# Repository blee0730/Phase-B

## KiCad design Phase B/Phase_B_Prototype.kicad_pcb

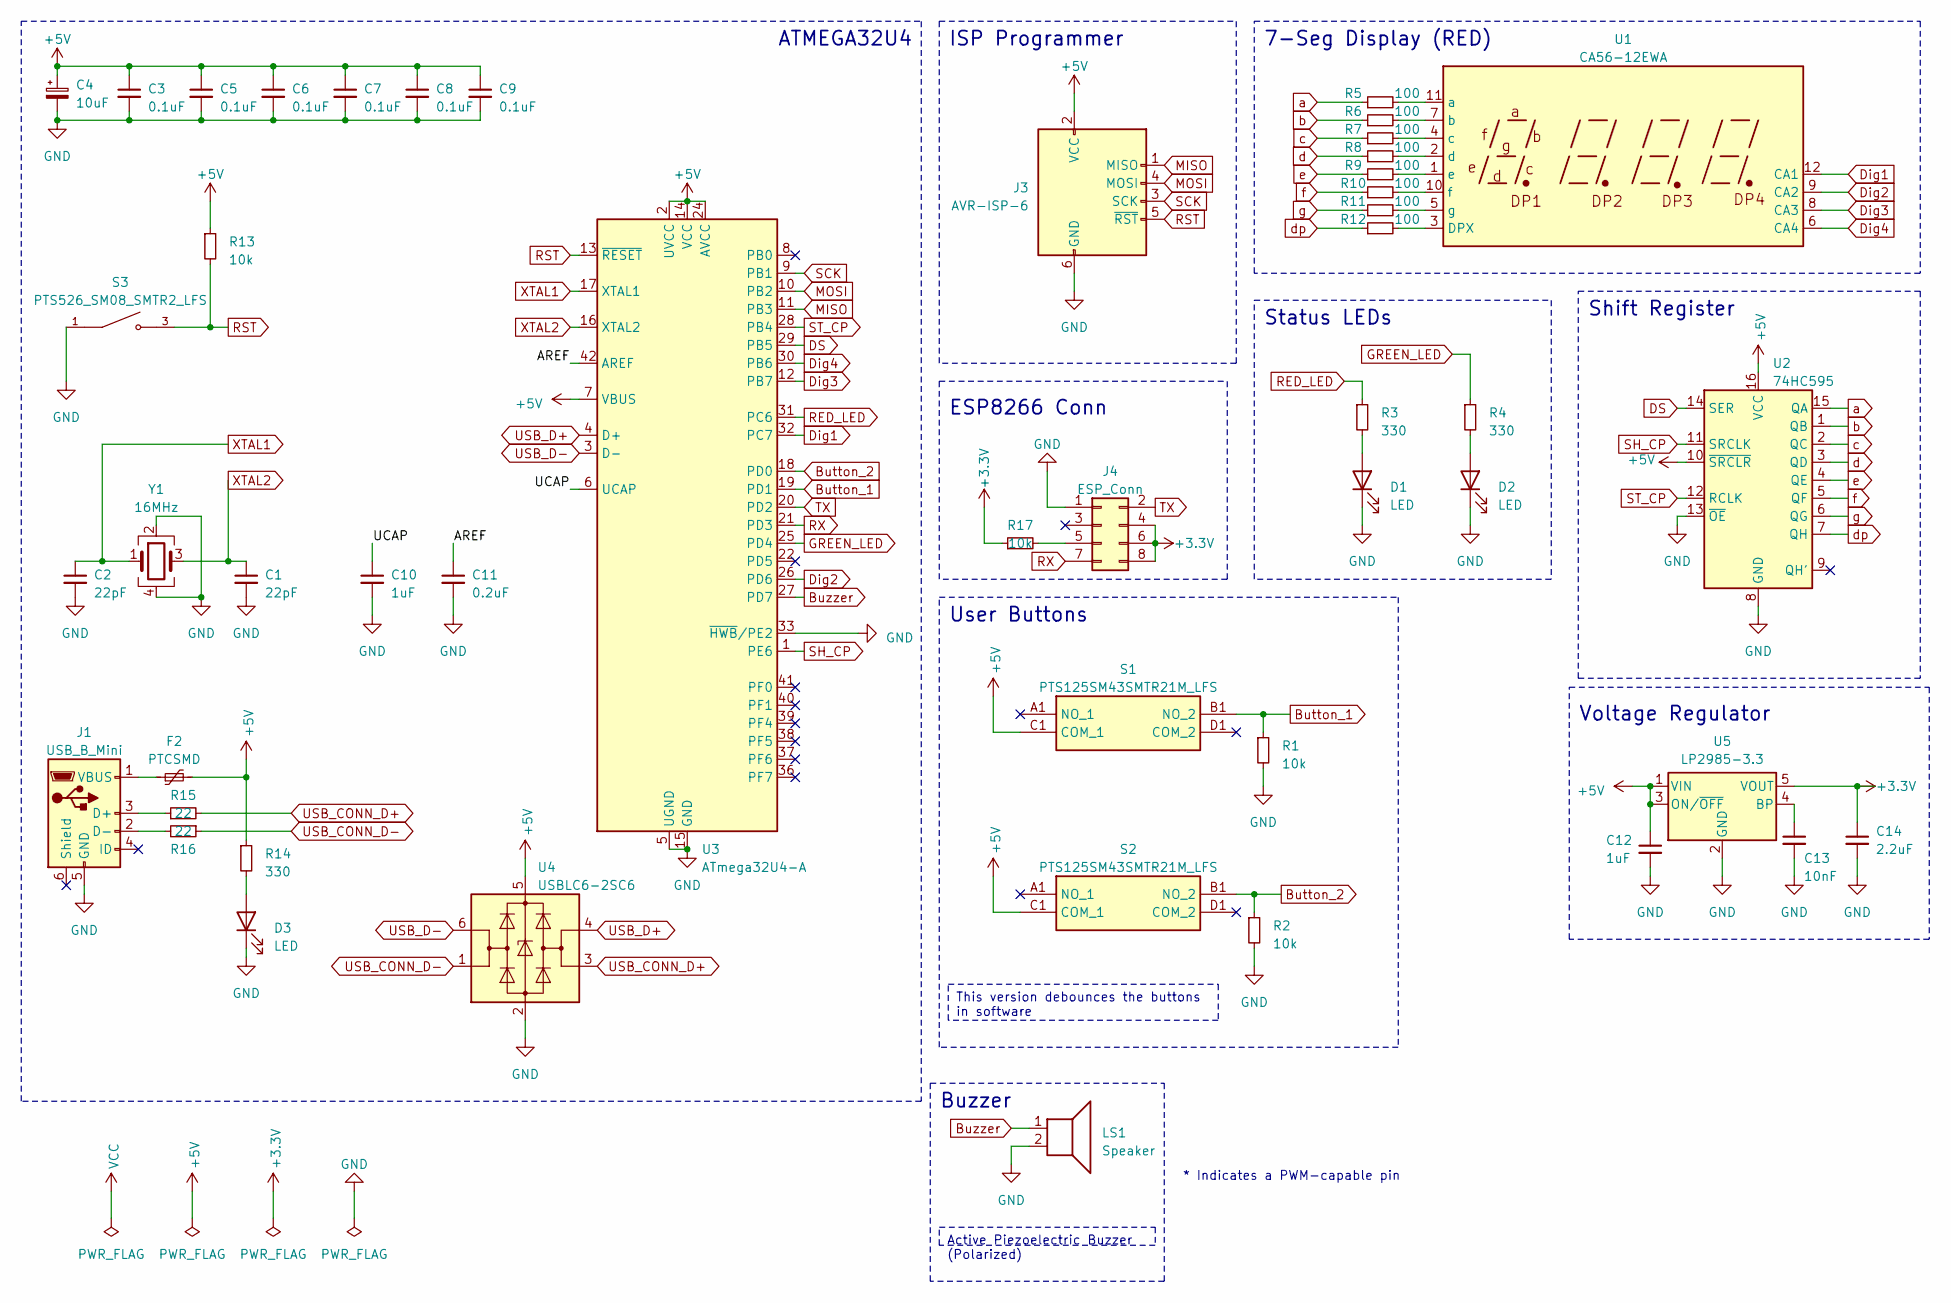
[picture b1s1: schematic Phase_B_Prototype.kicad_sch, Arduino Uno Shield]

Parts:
C1, C2: 22pF; C_0603_1608Metric
C3, C5, C6, C7, C8, C9: 0.1uF; C_0603_1608Metric
C4: 10uF; C_0805_2012Metric
C10, C12: 1uF; C_0603_1608Metric
C11: 0.2uF; C_0603_1608Metric
C13: 10nF; C_0603_1608Metric
C14: 2.2uF; C_0603_1608Metric
D1, D2, D3: LED; LED_0805_2012Metric
F2: PTCSMD; Fuse_1812_4532Metric
J1: USB_B_Mini; USB_Mini-B_Lumberg_2486_01_Horizontal
J3: AVR-ISP-6; PinSocket_2x03_P2.54mm_Vertical
J4: ESP_Conn; PinSocket_2x04_P2.54mm_Vertical
LS1: Speaker; Buzzer_12x9.5RM7.6
R1, R2, R13, R17: 10k; R_0603_1608Metric
R3, R4, R14: 330; R_0805_2012Metric
R5, R6, R7, R8, R9, R10, R11, R12: 100; R_0805_2012Metric
R15, R16: 22; R_0603_1608Metric
S1, S2: PTS125SM43SMTR21M_LFS; PTS125_SMD_Button; Manufacturer_Part_Number PTS125SM43SMTR21M LFS; Mouser Part Number 611-PTS125S43SMTRLFS
S3: PTS526_SM08_SMTR2_LFS; PTS526_SMD_Button; PARTREV 20 mar 19
U1: CA56-12EWA
U2: 74HC595; TSSOP-16_4.4x5mm_P0.65mm
U3: ATmega32U4-A; TQFP-44_10x10mm_P0.8mm
U4: USBLC6-2SC6; SOT-23-6
U5: LP2985-3.3; SOT-23-5
Y1: 16MHz; Crystal_SMD_Abracon_ABM8G-4Pin_3.2x2.5mm

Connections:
+3.3V: C14.1, J4.4, J4.6, J4.8, R17.1, U5.5 (VOUT)
+5V: C3.1, C4.1, C5.1, C6.1, C7.1, C8.1, C9.1, C12.1, F2.2, J3.2 (VCC), R13.1, R14.1, S1.C1 (COM_1), S2.C1 (COM_1), U2.10 (~SRCLR), U2.16 (VCC), U3.2 (UVCC), U3.7 (VBUS), U3.14 (VCC), U3.24 (AVCC), U3.34 (VCC), U3.44 (AVCC), U4.5 (VBUS), U5.1 (VIN), U5.3 (ON/~OFF)
/AREF: C11.1, U3.42 (AREF)
/UCAP: C10.1, U3.6 (UCAP)
Button_1: R1.1, S1.B1 (NO_2), U3.19 (PD1)
Button_2: R2.1, S2.B1 (NO_2), U3.18 (PD0)
Buzzer: LS1.1, U3.27 (PD7)
DS: U2.14 (SER), U3.29 (PB5)
Dig1: U1.12 (CA1), U3.32 (PC7)
Dig2: U1.9 (CA2), U3.26 (PD6)
Dig3: U1.8 (CA3), U3.12 (PB7)
Dig4: U1.6 (CA4), U3.30 (PB6)
GND: C1.2, C2.2, C3.2, C4.2, C5.2, C6.2, C7.2, C8.2, C9.2, C10.2, C11.2, C12.2, C13.2, C14.2, D1.1 (K), D2.1 (K), D3.1 (K), J1.5 (GND), J3.6 (GND), J4.1, LS1.2, R1.2, R2.2, S3.1, U2.8 (GND), U2.13 (~OE), U3.5 (UGND), U3.15 (GND), U3.23 (GND), U3.33 (~HWB/PE2), U3.35 (GND), U3.43 (GND), U4.2 (GND), U5.2 (GND), Y1.2, Y1.4
GREEN_LED: R4.1, U3.25 (PD4)
MISO: J3.1 (MISO), U3.11 (PB3)
MOSI: J3.4 (MOSI), U3.10 (PB2)
unnamed: D1.2 (A), R3.2
unnamed: D2.2 (A), R4.2
unnamed: D3.2 (A), R14.2
unnamed: J1.3 (D+), R15.1
unnamed: J1.2 (D-), R16.2
unnamed: F2.1, J1.1 (VBUS)
unnamed: J4.5, R17.2
unnamed: R12.2, U1.3 (DPX)
unnamed: R5.2, U1.11 (a)
unnamed: R6.2, U1.7 (b)
unnamed: R7.2, U1.4 (c)
unnamed: R8.2, U1.2 (d)
unnamed: R9.2, U1.1 (e)
unnamed: R10.2, U1.10 (f)
unnamed: R11.2, U1.5 (g)
unnamed: C13.1, U5.4 (BP)
RED_LED: R3.1, U3.31 (PC6)
RST: J3.5 (~RST), R13.2, S3.3, U3.13 (~RESET)
RX: J4.7, U3.21 (PD3)
SCK: J3.3 (SCK), U3.9 (PB1)
SH_CP: U2.11 (SRCLK), U3.1 (PE6)
ST_CP: U2.12 (RCLK), U3.28 (PB4)
TX: J4.2, U3.20 (PD2)
USB_CONN_D+: R15.2, U4.3 (I/O2)
USB_CONN_D-: R16.1, U4.1 (I/O1)
USB_D+: U3.4 (D+), U4.4 (I/O2)
USB_D-: U3.3 (D-), U4.6 (I/O1)
XTAL1: C2.1, U3.17 (XTAL1), Y1.1
XTAL2: C1.1, U3.16 (XTAL2), Y1.3
a: R5.1, U2.15 (QA)
b: R6.1, U2.1 (QB)
c: R7.1, U2.2 (QC)
d: R8.1, U2.3 (QD)
dp: R12.1, U2.7 (QH)
e: R9.1, U2.4 (QE)
f: R10.1, U2.5 (QF)
g: R11.1, U2.6 (QG)

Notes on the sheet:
Active Piezoelectric Buzzer (Polarized)
This version debounces the buttons in software
Shift Register
ESP8266 Conn
Voltage Regulator
ISP Programmer
Status LEDs
ATMEGA32U4
User Buttons
Buzzer
* Indicates a PWM-capable pin
7-Seg Display (RED)

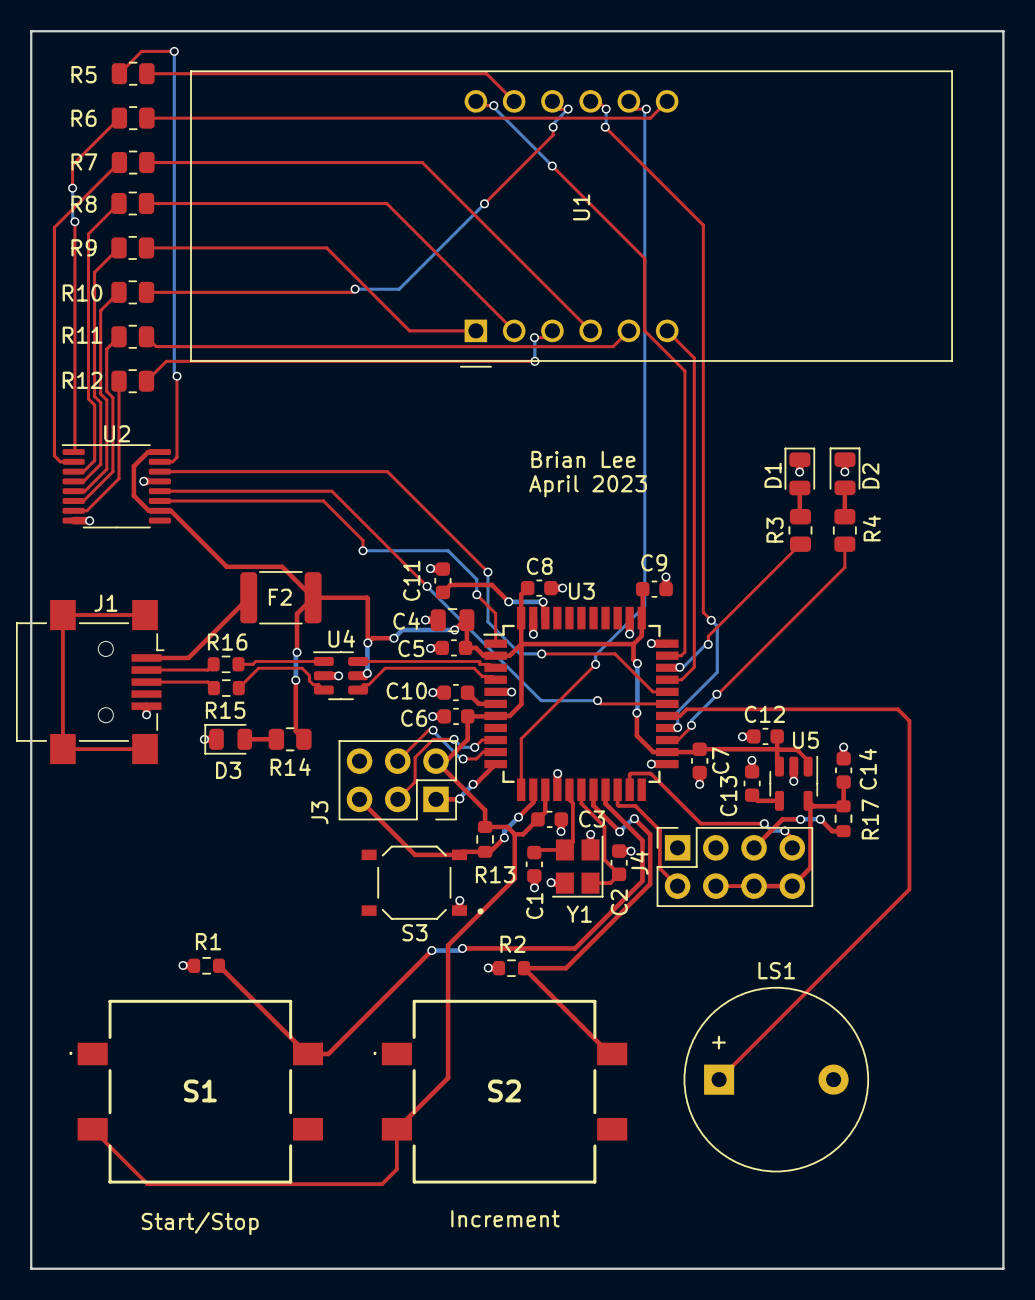
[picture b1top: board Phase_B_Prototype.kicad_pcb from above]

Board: 2 copper layers, 64.6 x 82.2 mm, 48 parts (0 on the bottom side), 53 nets.

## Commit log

2023-04-16 Phase B
